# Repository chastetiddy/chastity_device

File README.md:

# chastity_device
Chastity Device: Modification of jfedor's Flatbox R3

This is a modification of [jfedor's flatbox rev3](https://github.com/jfedor2/flatbox/tree/master/hardware-rev3).

I've made some minor rearrangements to the traces and button placement, as well as changing the tact switches to SMD parts. The board itself is a rounded rectangle as well, so as to use a stacked acrylic case.

To fully assemble you will need:

* [Brook PS3/PS4 fighting board PCB](https://www.brookaccessory.com/detail/58690501/)
* 12x Kailh low profile (choc v1) switches of your choice
* Compatible keycaps
* 6x Chicago Screws
* Acrylic panels for the case
* Soldering iron

You will need 1 each of acrylic panels 1-4. They must be the following thicknesses:

* 1 - Bottom Panel: Any
* 2 - Lower Mid Panel: Any
* 3 - Upper Mid Panel: 4.5mm. A thinner panel will not provide enough spacing for the top panel to sit flat above the tact switches.
* 4 - Top Panel: 3 mm. A thicker panel will render the tact switches unusable.

More detailed documentation forthcoming.

PCB design licensed under [CC BY-SA 4.0](https://creativecommons.org/licenses/by-sa/4.0/).

PCB design uses the following libraries:

* [keyswitches.pretty](https://github.com/daprice/keyswitches.pretty) by [daprice](https://github.com/daprice) ([CC BY-SA 4.0](https://creativecommons.org/licenses/by-sa/4.0/))
* [Type-C.pretty](https://github.com/ai03-2725/Type-C.pretty) by [ai03-2725](https://github.com/ai03-2725)

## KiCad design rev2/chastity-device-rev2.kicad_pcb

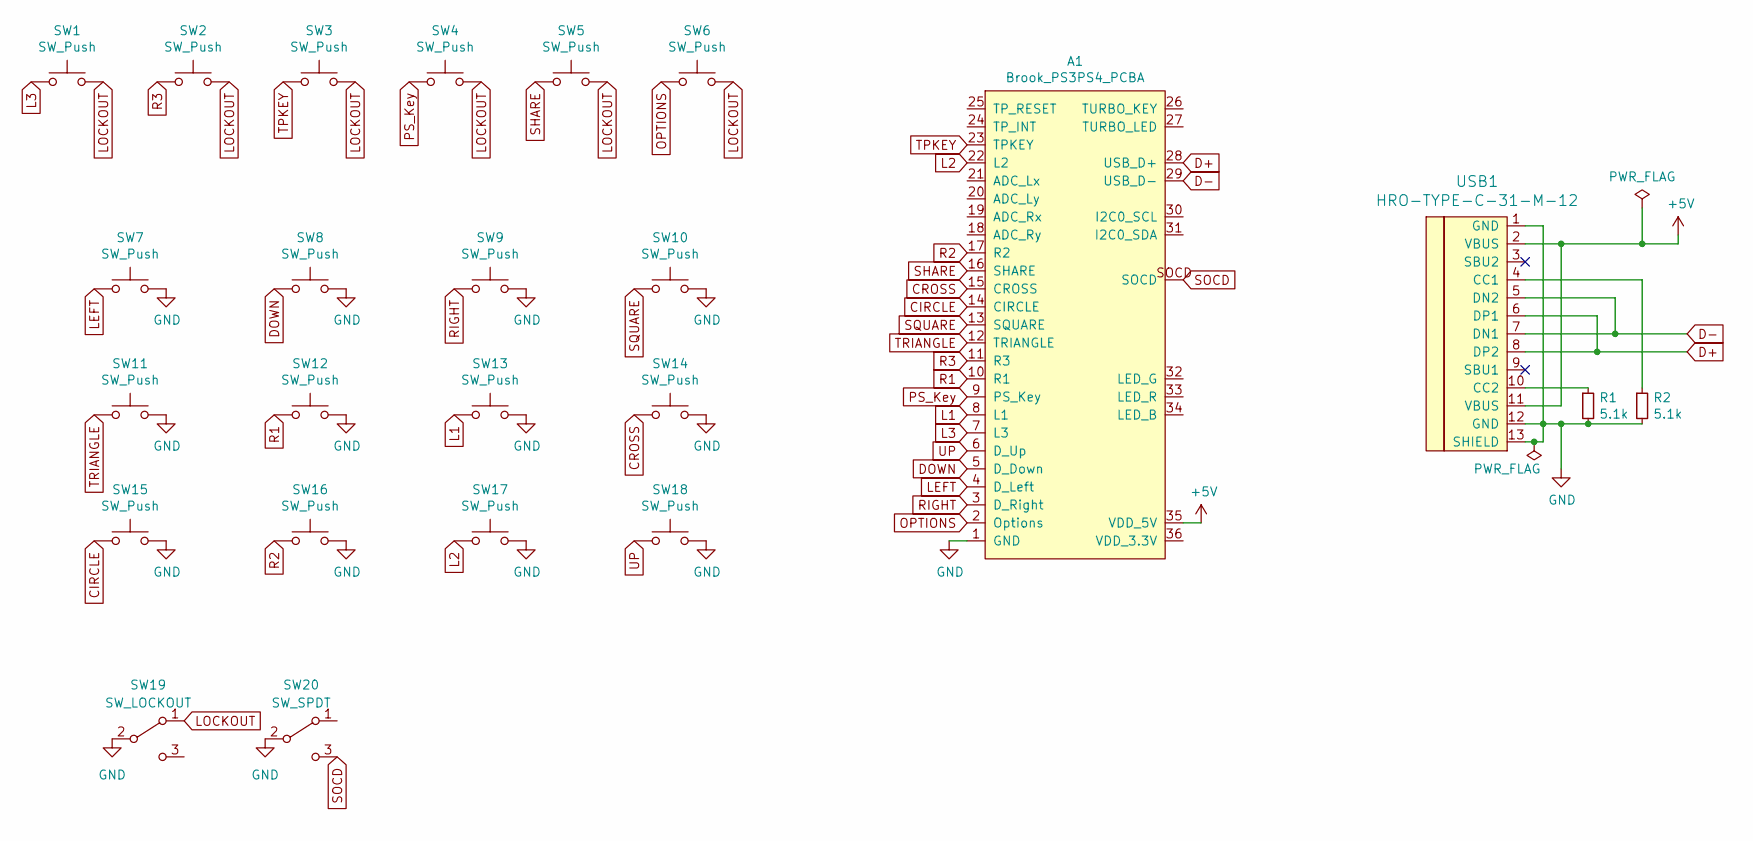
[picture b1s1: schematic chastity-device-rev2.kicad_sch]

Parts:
A1: Brook_PS3PS4_PCBA
R1, R2: 5.1k; R_0805_2012Metric; LCSC C27834
SW1, SW2, SW3, SW4, SW5, SW6: SW_Push; SW_Push_1P1T_NO_6x6mm_H9.5mm
SW7, SW8, SW9, SW10, SW11, SW12, SW13, SW14, SW15, SW16, SW17, SW18: SW_Push; Kailh_socket_PG1350_optional
SW19: SW_LOCKOUT; SW_SPDT_PCM12
SW20: SW_SPDT; SW_SPDT_PCM12
USB1: HRO-TYPE-C-31-M-12; HRO-TYPE-C-31-M-12-Assembly; LCSC C165948

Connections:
+5V: A1.35 (VDD_5V), USB1.2 (VBUS), USB1.11 (VBUS)
CIRCLE: A1.14 (CIRCLE), SW15.1
CROSS: A1.15 (CROSS), SW14.1
D+: A1.28 (USB_D+), USB1.6 (DP1), USB1.8 (DP2)
D-: A1.29 (USB_D-), USB1.5 (DN2), USB1.7 (DN1)
DOWN: A1.5 (D_Down), SW8.1
GND: A1.1 (GND), R1.2, R2.2, SW7.2, SW8.2, SW9.2, SW10.2, SW11.2, SW12.2, SW13.2, SW14.2, SW15.2, SW16.2, SW17.2, SW18.2, SW19.2 (B), SW20.2 (B), USB1.1 (GND), USB1.12 (GND), USB1.13 (SHIELD)
L1: A1.8 (L1), SW13.1
L2: A1.22 (L2), SW17.1
L3: A1.7 (L3), SW1.1
LEFT: A1.4 (D_Left), SW7.1
LOCKOUT: SW1.2, SW2.2, SW3.2, SW4.2, SW5.2, SW6.2, SW19.1 (A)
unnamed: R1.1, USB1.10 (CC2)
unnamed: R2.1, USB1.4 (CC1)
OPTIONS: A1.2 (Options), SW6.1
PS_Key: A1.9 (PS_Key), SW4.1
R1: A1.10 (R1), SW12.1
R2: A1.17 (R2), SW16.1
R3: A1.11 (R3), SW2.1
RIGHT: A1.3 (D_Right), SW9.1
SHARE: A1.16 (SHARE), SW5.1
SOCD: A1.SOCD, SW20.3 (C)
SQUARE: A1.13 (SQUARE), SW10.1
TPKEY: A1.23 (TPKEY), SW3.1
TRIANGLE: A1.12 (TRIANGLE), SW11.1
UP: A1.6 (D_Up), SW18.1

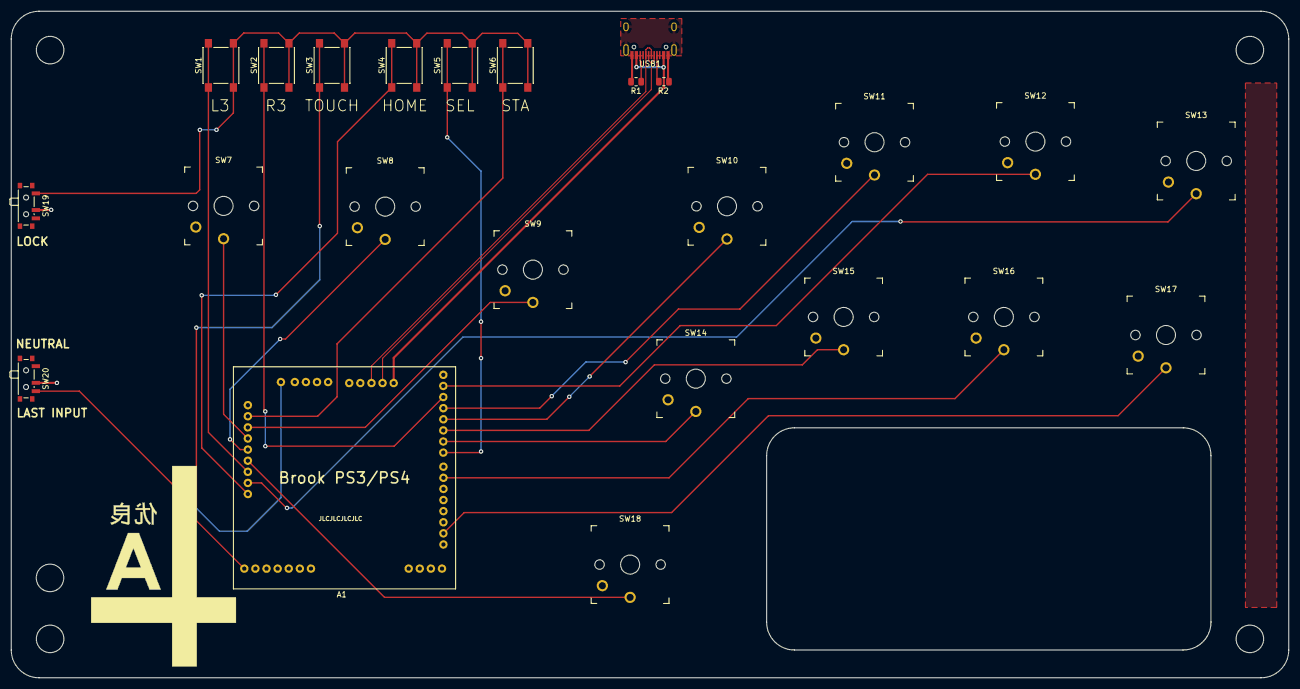
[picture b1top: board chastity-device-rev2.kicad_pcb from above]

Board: 2 copper layers, 230.0 x 120.0 mm, 24 parts (0 on the bottom side), 26 nets.

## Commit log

2022-08-16 Rev 1
2022-09-01 Updated Rev1 and added Rev2
    Reorganized folder structure.
    Added Rev1.1 redesign with ground pour and different hole placement. Acrylic design for 1.1 TBD.
    Added Rev2 with SOCD and lockout switches. Acrylic design for Rev2 TBD.
